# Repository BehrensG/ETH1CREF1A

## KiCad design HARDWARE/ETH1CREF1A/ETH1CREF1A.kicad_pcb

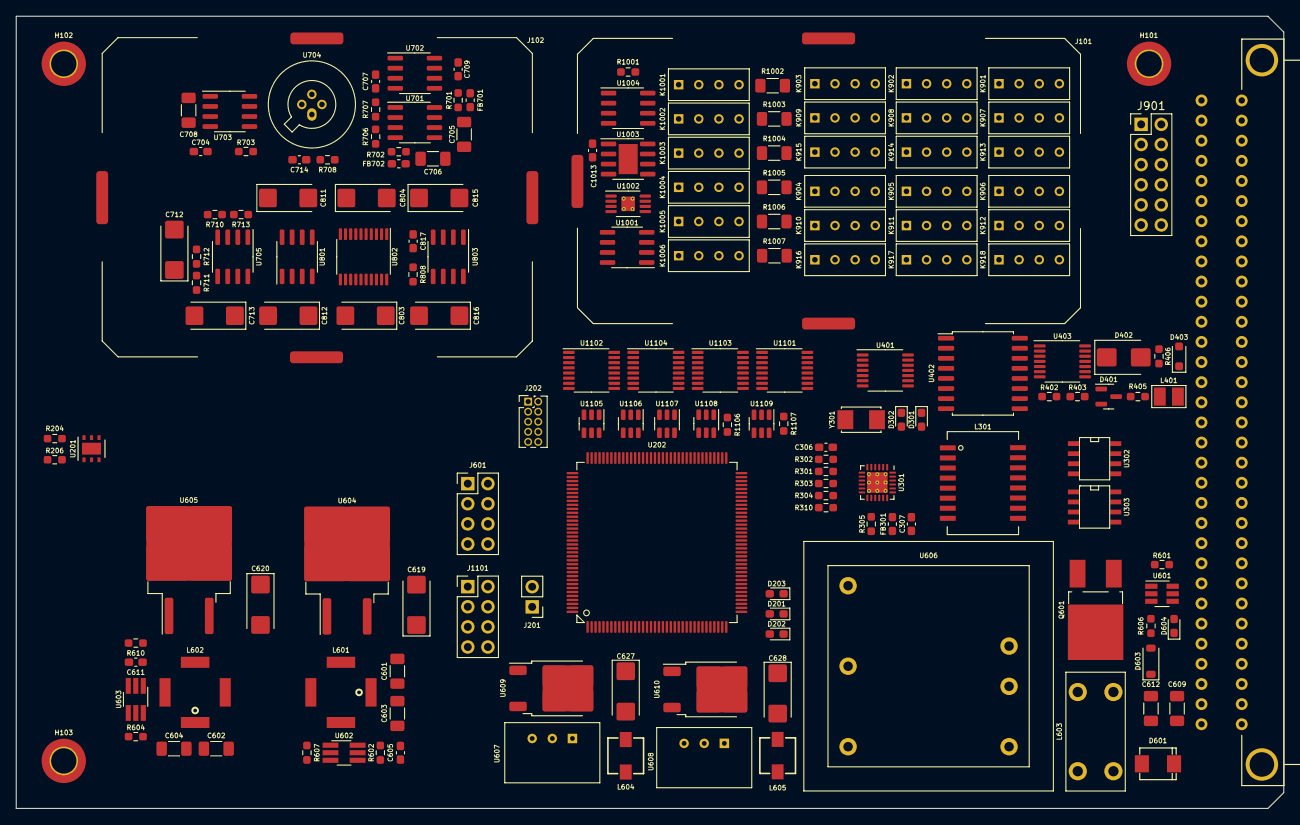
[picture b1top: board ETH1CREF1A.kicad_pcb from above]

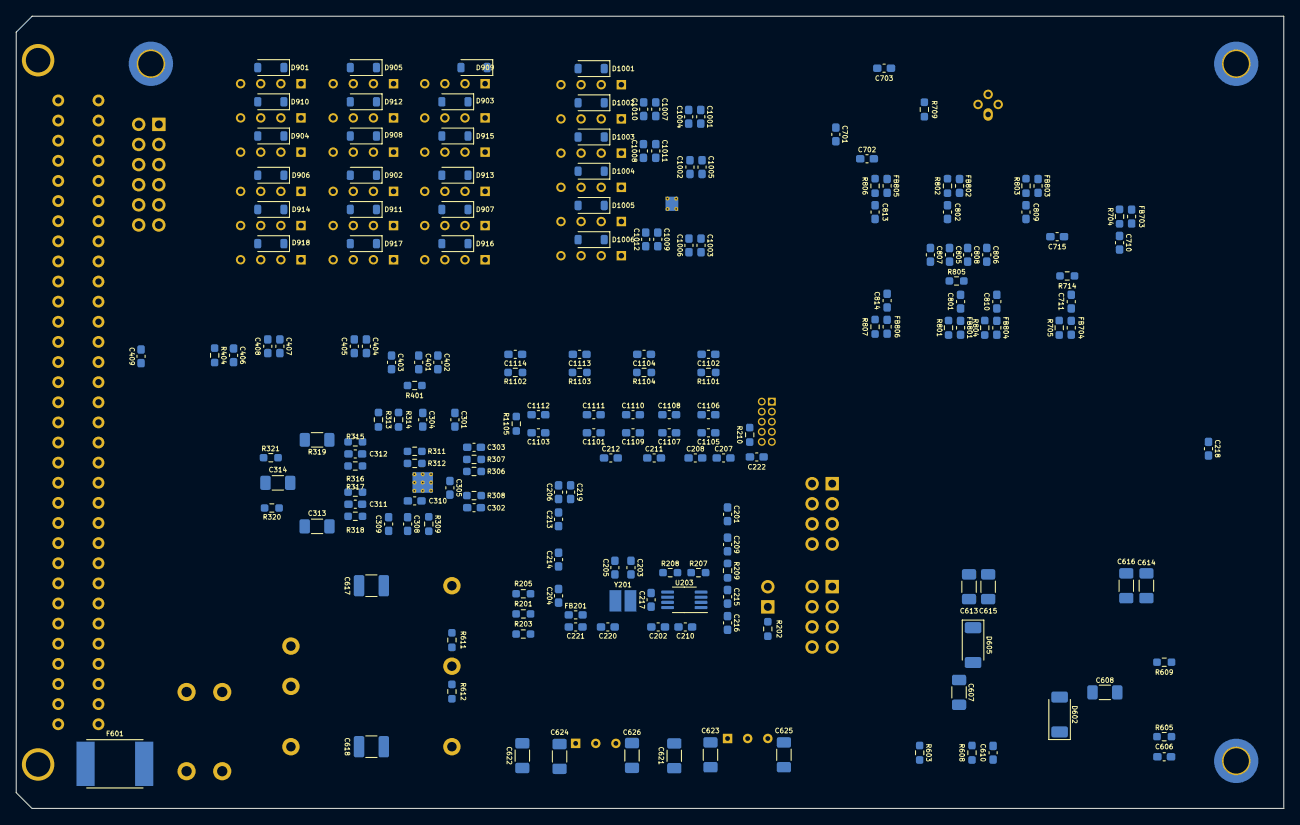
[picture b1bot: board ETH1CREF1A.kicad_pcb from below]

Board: 4 copper layers, 160.0 x 100.0 mm, 352 parts (186 on the bottom side), 209 nets, no tracks yet.

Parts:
C201, C202, C204, C207, C209, C211, C212, C213, C214, C215, C216, C217, C218, C219, C220, C222, C302, C305, C308, C309, C310, C311, C312, C401, C403, C404, C406, C408, C701, C702, C704, C710, C711, C714, C801, C802, C805, C806, C809, C810, C813, C814, C1001, C1002, C1003, C1007, C1008, C1009, C1101, C1102, C1103, C1104, C1105, C1106, C1107, C1108, C1109, C1110, C1111, C1112, C1113, C1114: 100n; C_0603_1608Metric_Pad1.08x0.95mm_HandSolder
C203, C205, C301, C304: 8p; C_0603_1608Metric_Pad1.08x0.95mm_HandSolder
C206, C208, C703, C707, C709: 2u2; C_0603_1608Metric_Pad1.08x0.95mm_HandSolder
C210, C221, C306, C307, C402, C405, C407, C605, C606, C807, C808, C1004, C1005, C1006, C1010, C1011, C1012: 1u; C_0603_1608Metric_Pad1.08x0.95mm_HandSolder
C303: 470p; C_0603_1608Metric_Pad1.08x0.95mm_HandSolder
C313, C314: 1n/1kV; C_1206_3216Metric_Pad1.33x1.80mm_HandSolder
C409: 47p; C_0603_1608Metric_Pad1.08x0.95mm_HandSolder
C601, C602, C621, C622, C623, C624: 10u/50V; C_1206_3216Metric_Pad1.33x1.80mm_HandSolder
C603, C604, C613, C614, C615, C616: 4u7/50V; C_1206_3216Metric_Pad1.33x1.80mm_HandSolder
C607, C608: 1u/HC; C_1206_3216Metric_Pad1.33x1.80mm_HandSolder
C609, C612: 2u2/50V; C_1206_3216Metric_Pad1.33x1.80mm_HandSolder
C610, C611: 4p7; C_0603_1608Metric_Pad1.08x0.95mm_HandSolder
C617, C618: 330p/2kV; C_1210_3225Metric_Pad1.33x2.70mm_HandSolder
C619, C620, C627, C628, C712, C713, C803, C804, C811, C812, C815, C816: 10u/35V; CP_EIA-6032-28_Kemet-C_Pad2.25x2.35mm_HandSolder
C625, C626: 10u/16V; C_1206_3216Metric_Pad1.33x1.80mm_HandSolder
C705, C706, C708: 10u/35V; C_1206_3216Metric_Pad1.33x1.80mm_HandSolder
C715, C817: 10p; C_0603_1608Metric_Pad1.08x0.95mm_HandSolder
C1013: 200p; C_0603_1608Metric_Pad1.08x0.95mm_HandSolder
D201: BLUE; LED_0603_1608Metric_Pad1.05x0.95mm_HandSolder
D202, D604: RED; LED_0603_1608Metric_Pad1.05x0.95mm_HandSolder
D203, D302: GREEN; LED_0603_1608Metric_Pad1.05x0.95mm_HandSolder
D301: YELLOW; LED_0603_1608Metric_Pad1.05x0.95mm_HandSolder
D401: BAV99; SOT-23
D402: SMBJ5.0A; D_SMB
D403: SD36C-01FTG; D_SOD-323_HandSoldering
D601: SM6T30AY; DO_214AA_REV
D602, D605: PMEG6010EP,115; D_SOD-128
D603: MMSZ5249B; D_SOD-123
D901, D902, D903, D904, D905, D906, D907, D908, D909, D910, D911, D912, D913, D914, D915, D916, D917, D918, D1001, D1002, D1003, D1004, D1005, D1006: 1N4148W; D_SOD-123
F601: MF-LSMF185/33X; Fuse_SMD2920
FB201, FB301, FB701, FB702, FB703, FB704, FB801, FB802, FB803, FB804, FB805, FB806: 600; L_0603_1608Metric_Pad1.05x0.95mm_HandSolder
H101, H102, H103: MountingHole; MountingHole_3.2mm_M3_DIN965_Pad_TopBottom
J101: MS638-10F
J102: MS548-10F
J201: Conn_02x01; PinHeader_1x02_P2.54mm_Vertical
J202: 20021111-00010T4LF; PinHeader_2x05_P1.27mm_Vertical
J501: C64AC; Socket_DIN41612-CaseC1-AC-Male-64Pin-2rows
J601, J1101: Conn_02x04_Odd_Even; PinHeader_2x04_P2.54mm_Vertical
J901: Conn_02x06_Odd_Even; PinHeader_2x06_P2.54mm_Vertical
K901, K902, K903, K904, K905, K906, K907, K908, K909, K910, K911, K912, K913, K914, K915, K916, K917, K918, K1001, K1002, K1003, K1004, K1005, K1006: 9012
L301: 749010012A
L401: CW252016-R33G; CW252016
L601, L602: 74489440068
L603: 7448014501
L604, L605: TCK-141
Q601: IRFR5410; TO-252-2_Rectifier
R201, R205: 680; R_0603_1608Metric_Pad0.98x0.95mm_HandSolder
R202, R209, R210, R303, R306, R307, R308, R309, R311, R401, R805, R1101, R1102, R1103, R1104: 10k; R_0603_1608Metric_Pad0.98x0.95mm_HandSolder
R203: 560; R_0603_1608Metric_Pad0.98x0.95mm_HandSolder
R204, R206, R207, R208: 4k7; R_0603_1608Metric_Pad0.98x0.95mm_HandSolder
R301, R302, R304, R305: 33; R_0603_1608Metric_Pad0.98x0.95mm_HandSolder
R310: 1k5; R_0603_1608Metric_Pad0.98x0.95mm_HandSolder
R312: 12k1; R_0603_1608Metric_Pad0.98x0.95mm_HandSolder
R313, R314: 270; R_0603_1608Metric_Pad0.98x0.95mm_HandSolder
R315, R316, R317, R318: 49R9; R_0603_1608Metric_Pad0.98x0.95mm_HandSolder
R319: 1M/1kV; R_1206_3216Metric_Pad1.30x1.75mm_HandSolder
R320, R321: 75/1%; R_0603_1608Metric_Pad0.98x0.95mm_HandSolder
R402: 14k7; R_0603_1608Metric_Pad0.98x0.95mm_HandSolder
R403: 100; R_0603_1608Metric_Pad0.98x0.95mm_HandSolder
R404, R1106: 1k; R_0603_1608Metric_Pad0.98x0.95mm_HandSolder
R405: 47; R_0603_1608Metric_Pad0.98x0.95mm_HandSolder
R406: 51R1; R_0603_1608Metric_Pad0.98x0.95mm_HandSolder
R601: 100k; R_0603_1608Metric_Pad0.98x0.95mm_HandSolder
R602, R604, R607, R609: 1M; R_0603_1608Metric_Pad0.98x0.95mm_HandSolder
R603, R605: 287k; R_0603_1608Metric_Pad0.98x0.95mm_HandSolder
R606: 330; R_0603_1608Metric_Pad0.98x0.95mm_HandSolder
R608: 97k6; R_0603_1608Metric_Pad0.98x0.95mm_HandSolder
R610: 46k4; R_0603_1608Metric_Pad0.98x0.95mm_HandSolder
R611, R612: OPT; R_0603_1608Metric_Pad0.98x0.95mm_HandSolder
R701, R702, R704, R705, R801, R802, R803, R804, R806, R807: 10; R_0603_1608Metric_Pad0.98x0.95mm_HandSolder
R703, R709, R808, R1105, R1107: 0; R_0603_1608Metric_Pad0.98x0.95mm_HandSolder
R706: 5k/.1%; R_0603_1608Metric_Pad0.98x0.95mm_HandSolder
R707: 2k/.1%; R_0603_1608Metric_Pad0.98x0.95mm_HandSolder
R708: 7k5; R_0603_1608Metric_Pad0.98x0.95mm_HandSolder
R710: 6k98/.1%; R_0603_1608Metric_Pad0.98x0.95mm_HandSolder
R711, R714: 10k/.1%; R_0603_1608Metric_Pad0.98x0.95mm_HandSolder
R712: 1k96/.1%; R_0603_1608Metric_Pad0.98x0.95mm_HandSolder
R713: 3k01/.1%; R_0603_1608Metric_Pad0.98x0.95mm_HandSolder
R1001: 2k; R_0603_1608Metric_Pad0.98x0.95mm_HandSolder
R1002: TNPV12061M00BYEN; R_1206_3216Metric_Pad1.30x1.75mm_HandSolder
R1003: TNPU1206100KBZEN00; R_1206_3216Metric_Pad1.30x1.75mm_HandSolder
R1004: TNPU120610K0AWEN00; R_1206_3216Metric_Pad1.30x1.75mm_HandSolder
R1005: TNPU12061K00AWEN00; R_1206_3216Metric_Pad1.30x1.75mm_HandSolder
R1006: TNPU1206100RAZEN00; R_1206_3216Metric_Pad1.30x1.75mm_HandSolder
R1007: RNCF1206AKT10R0; R_1206_3216Metric_Pad1.30x1.75mm_HandSolder
U201: HDC1080; Texas_PWSON-N6
U202: STM32F429ZIT; TQFP-144_20x20mm_P0.5mm
U203: 24LC08B-E/MS; MSOP-8_3x3mm_P0.65mm
U301: LAN8742A; QFN-24-1EP_4x4mm_P0.5mm_EP2.6x2.6mm_ThermalVias
U302, U303: LC03-3.3; SO8E
U401: TXB0104PW; TSSOP-14_4.4x5mm_P0.65mm
U402: ADuM5402; SOIC-16W_7.5x10.3mm_P1.27mm
U403: 74AC125; TSSOP-14_4.4x5mm_P0.65mm
U601: MAX5902; SOT-23-6_Handsoldering
U602, U603: LT8330_S6; TSOT-23-6_HandSoldering
U604: MC7815CD2TG; TO-263-2
U605: MC7915CD2TR4G; TO-263-2
U606: THL15-2415WI; THL15
U607: TSR1-2490; TSR1
U608: TSR1-2450; TSR1
U609: LM1117DTX-5/NOPB; TO-252-2
U610: LM1117DTX-3.3/NOPB; TO-252-2
U701, U705, U801: AD8676BRZ; SOIC-8_3.9x4.9mm_P1.27mm
U702: MAX6350ESA+; SOIC-8_3.9x4.9mm_P1.27mm
U703: LT1021DCS8-7#PBF; SOIC-8_3.9x4.9mm_P1.27mm
U704: LM399H; LMx99
U802: AD5791ARUZ; TSSOP-20_4.4x6.5mm_P0.65mm
U803: AD8675ARZ; SOIC-8_3.9x4.9mm_P1.27mm
U1001: DG419DY; SOIC-8_3.9x4.9mm_P1.27mm
U1002: LT5400-3; MSOP-8-1EP_3x3mm_P0.65mm_EP1.73x1.85mm_ThermalVias
U1003: ADA4898-2; SOIC-8-1EP_3.9x4.9mm_P1.27mm_EP2.41x3.81mm
U1004: AD811JRZ; SOIC-8_3.9x4.9mm_P1.27mm
U1101, U1102, U1103, U1104: 74HCT595PW; TSSOP-16_4.4x5mm_P0.65mm
U1105, U1106, U1107, U1108, U1109: SN74LVC1T45DRLR; SOT-23-6
Y201: NX5032GA-16.000M; NX3225GD
Y301: NX5032GA-25.000000MHZ-LN-CD-1; NX5032GA

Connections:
+3.3V: C201.1, C202.1, C204.1, C207.1, C209.1, C210.1, C211.1, C212.1, C213.1, C214.1, C215.1, C216.1, C217.1, C218.1, C219.1, C220.1, C302.1, C305.1, C401.1, C402.1, C628.1, C806.1, C808.1, C1101.1, C1103.1, C1105.1, C1107.1, C1109.1, D201.2 (A), D202.2 (A), D203.2 (A), FB201.1, FB301.1, J202.1, J601.4, R202.2, R204.1, R206.1, R207.1, R208.1, R210.1, R306.1, R307.1, R308.1, R309.1, R310.1, R401.1, R805.2, U201.5 (VCC), U202.6 (VBAT), U202.17 (VDD), U202.30 (VDD), U202.39 (VDD), U202.52 (VDD), U202.62 (VDD), U202.72 (VDD), U202.84 (VDD), U202.95 (VDDUSB), U202.108 (VDD), U202.121 (VDD), U202.131 (VDD), U202.143 (PDR_ON), U202.144 (VDD), U203.8 (VCC), U301.9 (VDDIO), U401.1 (VCCA), U610.2 (VO), U802.6 (~RESET), U802.7 (~CLR), U802.10 (IOVCC), U1105.6 (VCCB), U1106.6 (VCCB), U1107.6 (VCCB), U1108.6 (VCCB), U1109.6 (VCCB)
+5V: C403.1, C404.1, C405.1, C627.1, C805.1, C807.1, C1102.1, C1104.1, C1106.1, C1108.1, C1110.1, C1111.1, C1112.1, C1113.1, C1114.1, D901.1 (K), D902.1 (K), D903.1 (K), D904.1 (K), D905.1 (K), D906.1 (K), D907.1 (K), D908.1 (K), D909.1 (K), D910.1 (K), D911.1 (K), D912.1 (K), D913.1 (K), D914.1 (K), D915.1 (K), D916.1 (K), D917.1 (K), D918.1 (K), D1001.1 (K), D1002.1 (K), D1003.1 (K), D1004.1 (K), D1005.1 (K), D1006.1 (K), J601.2, K901.2, K902.2, K903.2, K904.2, K905.2, K906.2, K907.2, K908.2, K909.2, K910.2, K911.2, K912.2, K913.2, K914.2, K915.2, K916.2, K917.2, K918.2, K1001.2, K1002.2, K1003.2, K1004.2, K1005.2, K1006.2, R1101.2, R1102.2, R1103.2, R1104.2, R1106.2, U401.14 (VCCB), U402.1 (VDD1), U609.2 (VO), U802.9 (VCC), U1001.5 (VL), U1101.10 (~SRCLR), U1101.16 (VCC), U1102.10 (~SRCLR), U1102.16 (VCC), U1103.10 (~SRCLR), U1103.16 (VCC), U1104.10 (~SRCLR), U1104.16 (VCC), U1105.1 (VCCA), U1106.1 (VCCA), U1107.1 (VCCA), U1108.1 (VCCA), U1109.1 (VCCA)
+5V_TRIG: C406.1, C407.1, C408.1, R404.1, U402.10 (VSEL), U402.16 (VISO), U403.14 (VCC)
+15VF: C619.1, C703.1, C704.1, C708.1, C1007.1, C1008.1, C1009.1, C1010.1, C1011.1, C1012.1, FB701.1, FB704.1, FB802.1, FB803.1, FB806.1, J601.1, R701.1, R705.1, R708.1, R802.1, R803.1, R807.1, U604.3 (OUT), U702.2 (IN), U703.2 (Vin), U704.3, U1001.4 (V+), U1003.8 (V+), U1004.7 (V+)
+24V: F601.1, J501.A31 (31A), J501.A32 (32A), J501.C31 (31C), J501.C32 (32C)
+24VF: C601.1, C602.1, C603.1, C604.1, C617.1, C621.1, C622.1, L601.1, L602.1, L604.1, L605.1, R602.1, R604.1, R611.1, U602.6 (VIN), U603.6 (VIN), U606.3 (+VOUT)
-15VF: C620.2, C1001.1, C1002.1, C1003.1, C1004.1, C1005.1, C1006.1, FB702.1, FB703.1, FB801.1, FB804.1, FB805.1, J601.3, R702.1, R704.1, R801.1, R804.1, R806.1, U605.3 (VO), U704.4, U1001.7 (V-), U1003.4 (V-), U1003.9 (EP), U1004.4 (V-)
/Connect/EXT_TRIG: C409.1, D403.1 (A1), J501.A16 (16A), L401.1
/Connect/RX+: J501.A20 (20A), U303.8
/Connect/RX-: J501.A21 (21A), U303.5
/Connect/TX+: J501.C20 (20C), U302.8
/Connect/TX-: J501.C21 (21C), U302.5
/Current Source/AOUT: K907.1, K908.1, K909.1, K910.1, K911.1, K912.1, R1002.2, R1003.2, R1004.2, R1005.2, R1006.2, R1007.2, U1003.5 (+)
/Current Source/CS_SEL_R1Meg: D1001.2 (A), K1001.3, U1104.15 (QA)
/Current Source/CS_SEL_R1k: D1004.2 (A), K1004.3, U1104.3 (QD)
/Current Source/CS_SEL_R10: D1006.2 (A), K1006.3, U1104.5 (QF)
/Current Source/CS_SEL_R10k: D1003.2 (A), K1003.3, U1104.2 (QC)
/Current Source/CS_SEL_R100: D1005.2 (A), K1005.3, U1104.4 (QE)
/Current Source/CS_SEL_R100k: D1002.2 (A), K1002.3, U1104.1 (QB)
/Current Source/CS_SEL_VSOUR: U1001.6, U1104.6 (QG)
/Current Source/VOUT: C817.2, K901.1, K902.1, K903.1, K904.1, K905.1, K906.1, R808.2, U803.6, U1001.8
/DAC/DAC_+15V: C802.1, C804.1, FB802.2, R802.2, U802.5 (VDD)
/DAC/DAC_-15V: C801.1, C803.2, FB801.2, R801.2, U802.18 (VSS)
/DAC/OPAMP_+15V: C814.1, C816.1, FB806.2, R807.2, U803.7 (V+)
/DAC/OPAMP_-15V: C813.1, C815.1, FB805.2, R806.2, U803.4 (V-)
/DAC/REF_-10V: R714.2, U705.7, U801.3 (+)
/DAC/SCLK: U202.111 (PC10,SPI3_SCK,I2S3_CK,USART3_TX,UART4_T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), U802.13 (SCLK)
/DAC/SDIN: U202.113 (PC12,SPI3_MOSI,I2S3_SD,USART3_CK,UART5_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), U802.12 (SDIN)
/DAC/SDO: U202.112 (PC11,I2S3ext_SD,SPI3_MISO,USART3_RX,UAR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), U802.11 (SDO)
/DAC/~SYNC: R805.1, U202.110 (PA15,JTDI,TIM2_CH1,TIM2_ETR,SPI1_NSS,SP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), U802.14 (~SYNC)
/Ethernet/ETH_RXN: L301.8 (RD-), R318.2, U301.22 (RXN)
/Ethernet/ETH_RXP: L301.6 (RD+), R317.2, U301.23 (RXP)
/Ethernet/ETH_TXN: L301.3 (TD-), R316.2, U301.20 (TXN)
/Ethernet/ETH_TXP: L301.1 (TD+), R315.2, U301.21 (TXP)
/Ethernet/MODE0: R301.1, R306.2, U301.8 (RXD0/MODE0)
/Ethernet/MODE1: R302.1, R307.2, U301.7 (RXD1/MODE1)
/Ethernet/MODE2: R304.1, R308.2, U301.11 (CRS_DV/MODE2)
/Ethernet/REFCLK0: R305.1, R309.2, U301.14 (~INT/REFCLK0)
/Ethernet/REF_CLK: R305.2, U202.35 (PA1,TIM2_CH2,TIM5_CH2,USART2_RTS,UART4_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)
/Ethernet/RMII_CRS_DV: R304.2, U202.43 (PA7,TIM1_CH1N,TIM3_CH2,TIM8_CH1N,SPI1_M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)
/Ethernet/RMII_MDC: U202.27 (PC1,ETH_MDC,EVENTOUT,ADC1_IN11,ADC2_IN1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), U301.13 (MDC)
/Ethernet/RMII_MDIO: R310.2, U202.36 (PA2,TIM2_CH3,TIM5_CH3,TIM9_CH1,USART2_T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), U301.12 (MDIO)
/Ethernet/RMII_RXD0: R301.2, U202.44 (PC4,ETH_MII_RXD0,ETH__RMII_RXD0,EVENTOU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)
/Ethernet/RMII_RXD1: R302.2, U202.45 (PC5,ETH_MII_RXD1,ETH__RMII_RXD1,EVENTOU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)
/Ethernet/RMII_TXD0: U202.128 (PG13,SPI6_SCK,USART6_CTS,ETH_MII_TXD0,E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), U301.17 (TXD0)
/Ethernet/RMII_TXD1: U202.129 (PG14,SPI6_MOSI,USART6_TX,ETH_MII_TXD1,E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), U301.18 (TXD1)
/Ethernet/RMII_TXEN: U202.126 (PG11,ETH_MII_TX_EN,ETH__RMII_TX_EN,FMC_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), U301.16 (TXEN)
/GPIO/MODE_I2C_SCL: J1101.1, U202.100 (PA8,MCO1,TIM1_CH1,I2C3_SCL,USART1_CK,OT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)
/GPIO/MODE_I2C_SDA: J1101.3, U202.99 (PC9,MCO2,TIM3_CH4,TIM8_CH4,I2C3_SDA,I2S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)
/GPIO/QH: U202.75 (PB14,TIM1_CH2N,TIM8_CH2N,SPI2_MISO,I2S2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), U1108.4 (B)
/GPIO/RCLK: U202.73 (PB12,TIM1_BKIN,I2C2_SMBA,SPI2_NSS,I2S2_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), U1107.4 (B)
/GPIO/SER: U202.76 (PB15,RTC_REFIN,TIM1_CH3N,TIM8_CH3N,SPI2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), U1105.4 (B)
/GPIO/SPI5_MISO: J1101.4, U202.20 (PF8,SPI5_MISO,SAI1_SCK_B,TIM13_CH1,FMC_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)
/GPIO/SPI5_MOSI: J1101.6, U202.21 (PF9,SPI5_MOSI,SAI1_FS_B,TIM14_CH1,FMC_C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)
/GPIO/SPI5_SCK: J1101.2, U202.19 (PF7,TIM11_CH1,SPI5_SCK,SAI1_MCLK_B,UART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)
/GPIO/SRCLK: U202.74 (PB13,TIM1_CH1N,SPI2_SCK,I2S2_CK,USART3_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), U1106.4 (B)
/GPIO/nOE: U202.70 (PB11,TIM2_CH4,I2C2_SDA,USART3_RX,OTG_HS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), U1109.4 (B)
/GPIO/relay0: D901.2 (A), K901.3, U1104.7 (QH)
/GPIO/relay1: D906.2 (A), K906.3, U1103.15 (QA)
/GPIO/relay2: D911.2 (A), K911.3, U1103.1 (QB)
/GPIO/relay3: D916.2 (A), K916.3, U1103.2 (QC)
/GPIO/relay4: D902.2 (A), K902.3, U1103.3 (QD)
/GPIO/relay5: D907.2 (A), K907.3, U1103.4 (QE)
/GPIO/relay6: D912.2 (A), K912.3, U1103.5 (QF)
/GPIO/relay7: D915.2 (A), K915.3, U1103.6 (QG)
/GPIO/relay8: D903.2 (A), K903.3, U1103.7 (QH)
/GPIO/relay9: D908.2 (A), K908.3, U1101.15 (QA)
/GPIO/relay10: D913.2 (A), K913.3, U1101.1 (QB)
/GPIO/relay11: D917.2 (A), K917.3, U1101.2 (QC)
/GPIO/relay12: D904.2 (A), K904.3, U1101.3 (QD)
/GPIO/relay13: D909.2 (A), K909.3, U1101.4 (QE)
/GPIO/relay14: D914.2 (A), K914.3, U1101.5 (QF)
/GPIO/relay15: D918.2 (A), K918.3, U1101.6 (QG)
/GPIO/relay16: D905.2 (A), K905.3, U1101.7 (QH)
/GPIO/relay17: D910.2 (A), K910.3, U1102.15 (QA)
/MCU/EEPROM_SCL: R208.2, U202.11 (PF1,I2C2_SCL,FMC_A1,EVENTOUT), U203.6 (SCL)
/MCU/EEPROM_SDA: R207.2, U202.10 (PF0,I2C2_SDA,FMC_A0,EVENTOUT), U203.5 (SDA)
/MCU/EEPROM_WP: U202.89 (PG4,FMC_A14,FMC_BA0,EVENTOUT), U203.7 (WP)
/MCU/LED_BLUE: R201.1, U202.48 (PB2,BOOT1,EVENTOUT)
/MCU/LED_GREEN: R205.1, U202.50 (PF12,FMC_A6,EVENTOUT)
/MCU/LED_RED: R203.1, U202.49 (PF11,SPI5_MOSI,FMC_SDNRAS,DCMI_D12,EVEN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)
/MCU/MCU_DEFAULT: J201.1, R202.1, U202.63 (PE10,TIM1_CH2N,FMC_D7,EVENTOUT)
/MCU/MCU_VDDA: C221.1, FB201.2, U202.32 (VREF+), U202.33 (VDDA)
/MCU/NRST: C222.1, J202.10, R210.2, U202.25 (NRST), U301.15 (~RST)
/MCU/SENS_SCL: R204.2, U201.6 (SCL), U202.136 (PB6,TIM4_CH1,I2C1_SCL,USART1_TX,CAN2_TX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)
/MCU/SENS_SDA: R206.2, U201.1 (SDA), U202.137 (PB7,TIM4_CH2,I2C1_SDA,USART1_RX,FMC_NL,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)
/MCU/TCK_SWCLK: J202.4, U202.109 (PA14,JTCK-SWCLK,EVENTOUT)
/MCU/TMS_SWDIO: J202.2, U202.105 (PA13,JTMS-SWDIO,EVENTOUT)
/MCU/TRIG_EN: U202.60 (PE9,TIM1_CH1,FMC_D6,EVENTOUT), U401.2 (A1)
/MCU/TRIG_IN: U202.58 (PE7,TIM1_ETR,UART7_Rx,FMC_D4,EVENTOUT), U401.4 (A3)
/MCU/TRIG_OUT: U202.59 (PE8,TIM1_CH1N,UART7_Tx,FMC_D5,EVENTOUT), U401.3 (A2)
/Reference Voltage/REF_+10V: C715.2, R711.1, R712.2, R713.2, U705.1, U801.5 (+)
/Relays/A_AOUT: J501.A2 (2A), J501.C2 (2C), J901.1, J901.2, K901.4, K907.4, K913.4
/Relays/B_AOUT: J501.A3 (3A), J501.C3 (3C), J901.3, J901.4, K902.4, K908.4, K914.4
/Relays/C_AOUT: J501.A4 (4A), J501.C4 (4C), J901.5, J901.6, K903.4, K909.4, K915.4
/Relays/D_AOUT: J501.A5 (5A), J501.C5 (5C), J901.7, J901.8, K904.4, K910.4, K916.4
/Relays/E_AOUT: J501.A6 (6A), J501.C6 (6C), J901.9, J901.10, K905.4, K911.4, K917.4
/Relays/F_AOUT: J501.A7 (7A), J501.C7 (7C), J901.11, J901.12, K906.4, K912.4, K918.4
/Trigger/EXT_TRIG_SIGN: R402.1, U402.12 (VIC), U403.3 (O)
/Trigger/TRIG_OUT_EN: U402.14 (VOA), U403.4 (EN), U403.10 (EN), U403.13 (EN)
/Trigger/TRIG_OUT_SIGN: U402.13 (VOB), U403.5 (D), U403.9 (D), U403.12 (D)
AGNDF: C201.2, C202.2, C203.2, C204.2, C205.2, C206.2, C207.2, C208.2, C209.2, C210.2, C211.2, C212.2, C213.2, C214.2, C215.2, C216.2, C217.2, C218.2, C219.2, C220.2, C221.2, C222.2, C301.2, C302.2, C303.2, C304.2, C305.2, C306.2, C307.2, C308.2, C309.2, C310.2, C311.2, C312.2, C313.2, C401.2, C402.2, C403.2, C404.2, C405.2, C601.2, C602.2, C603.2, C604.2, C605.2, C606.2, C613.2, C614.2, C615.2, C616.2, C618.1, C619.2, C620.1, C621.2, C622.2, C623.2, C624.2, C625.2, C626.2, C627.2, C628.2, C701.2, C702.2, C703.2, C704.2, C705.2, C706.2, C707.2, C708.2, C709.2, C710.2, C711.2, C712.1, C713.2, C714.2, C801.2, C802.2, C803.1, C804.2, C805.2, C806.2, C807.2, C808.2, C809.2, C810.2, C811.2, C812.2, C813.2, C814.2, C815.2, C816.2, C1001.2, C1002.2, C1003.2, C1004.2, C1005.2, C1006.2, C1007.2, C1008.2, C1009.2, C1010.2, C1011.2, C1012.2, C1101.2, C1102.2, C1103.2, C1104.2, C1105.2, C1106.2, C1107.2, C1108.2, C1109.2, C1110.2, C1111.2, C1112.2, C1113.2, C1114.2, D602.1 (K), J101.1 (Shield), J102.1 (Shield), J201.2, J202.3, J202.5, J601.5, J601.6, J601.7, J601.8, J1101.5, J1101.7, J1101.8, K913.1, K914.1, K915.1, K916.1, K917.1, K918.1, L601.3, R209.2, R303.2, R311.2, R312.1, R313.2, R314.2, R319.2, R603.2, R605.2, R608.2, R610.2, R612.2, R706.1, R710.1, R1105.2, U201.2 (GND), U202.16 (VSS), U202.31 (VSSA), U202.38 (VSS), U202.51 (VSS), U202.61 (VSS), U202.83 (VSS), U202.94 (VSS), U202.107 (VSS), U202.120 (VSS), U202.130 (VSS), U203.1 (A0), U203.2 (A1), U203.3 (A2), U203.4 (GND), U301.25 (VSS), U401.7 (GND), U402.2 (GND1), U402.8 (GND1), U602.2 (GND), U603.2 (GND), U604.2 (GND), U605.1 (GND), U606.5 (-VOUT), U607.2 (GND), U608.2 (GND), U609.1 (GND), U610.1 (GND), U701.5 (+), U702.4 (GND), U703.4 (GND), U704.2, U705.5 (+), U802.8 (~LDAC), U802.15 (DGND), U802.19 (AGND), U1001.2, U1001.3 (GND), U1002.8, U1002.9, U1101.8 (GND), U1102.8 (GND), U1103.8 (GND), U1104.8 (GND), U1105.2 (GND), U1105.5 (DIR), U1106.2 (GND), U1106.5 (DIR), U1107.2 (GND), U1107.5 (DIR), U1108.2 (GND), U1109.2 (GND), U1109.5 (DIR)
Earth: C313.1, C314.2, J501.A18 (18A), J501.A22 (22A), J501.C18 (18C), J501.C22 (22C), R319.1
GNDPWR: C609.2, C612.2, D601.2 (A), D604.1 (K), J501.A27 (27A), J501.A28 (28A), J501.C27 (27C), J501.C28 (28C), L603.1, U601.4 (GND)
GND_TRIG: C406.2, C407.2, C408.2, D401.1 (K), D402.2 (A), D403.2 (A2), J501.C16 (16C), R406.2, U402.9 (GNDISO), U402.15 (GNDISO), U403.1 (EN), U403.7 (GND)
unnamed: C314.1, R320.2, R321.2
unnamed: C409.2, R406.1
unnamed: D201.1 (K), R201.2
unnamed: D202.1 (K), R203.2
unnamed: D203.1 (K), R205.2
unnamed: D301.2 (A), R311.1, U301.2 (LED2/~INTSEL)
unnamed: D301.1 (K), R313.1
unnamed: D302.2 (A), U301.3 (LED1/REGOFF)
unnamed: D302.1 (K), R314.1
unnamed: D401.2 (A), D402.1 (K), R404.2
unnamed: D601.1 (K), F601.2, Q601.3 (S), R601.1, U601.1 (VS)
unnamed: C608.1, D602.2 (A), L602.2
unnamed: D603.2 (A), R606.1
unnamed: C609.1, C612.1, D603.1 (K), L603.2, Q601.2 (D), U601.2 (DRAIN)
unnamed: D604.2 (A), R606.2
unnamed: C607.1, D605.2 (A), L601.2
unnamed: C610.1, C613.1, C615.1, D605.1 (K), R607.1, U604.1 (IN)
unnamed: K1001.1, K1002.1, K1003.1, K1004.1, K1005.1, K1006.1, R1001.2, U1002.7, U1004.6
unnamed: K1001.4, R1002.1
unnamed: K1002.4, R1003.1
unnamed: K1003.4, R1004.1
unnamed: K1004.4, R1005.1
unnamed: K1005.4, R1006.1
unnamed: K1006.4, R1007.1
unnamed: L301.10 (CRX), R320.1
unnamed: L301.15 (CTX), R321.1
unnamed: L301.11 (RX+), U303.1
unnamed: L301.9 (RX-), U303.4
unnamed: L301.16 (TX+), U302.1
unnamed: L301.14 (TX-), U302.4
unnamed: L401.2, R405.2
unnamed: Q601.1 (G), U601.3 (GATE)
unnamed: R707.2, R709.2, U701.1
unnamed: R209.1, U202.138 (BOOT0)
unnamed: C203.1, U202.23 (PH0,EVENTOUT,OSC_IN), Y201.1
unnamed: C205.1, U202.24 (PH1,EVENTOUT,OSC_OUT), Y201.2
unnamed: C206.1, U202.71 (VCAP_1)
unnamed: C208.1, U202.106 (VCAP_2)
unnamed: R312.2, U301.24 (RBIAS)
unnamed: R303.1, U301.10 (RXER/PHYAD0)
unnamed: C303.1, C306.1, U301.6 (VDDCR)
unnamed: C301.1, U301.5 (XTAL1/CLKIN), Y301.2
unnamed: C304.1, U301.4 (XTAL2), Y301.1
unnamed: U401.13 (B1), U402.3 (VIA)
unnamed: U401.12 (B2), U402.4 (VIB)
unnamed: U401.11 (B3), U402.5 (VOC)
unnamed: R401.2, U401.8 (OE)
unnamed: R402.2, R403.1, U403.2 (D)
unnamed: D401.3 (K), R403.2, R405.1, U403.6 (O), U403.8 (O), U403.11 (O)
unnamed: R601.2, U601.6 (ON/~OFF)
unnamed: R602.2, R603.1, U602.4 (EN/UVLO)
unnamed: C610.2, R607.2, R608.1, U602.3 (FBX)
unnamed: C605.1, U602.5 (INTVCC)
unnamed: C607.2, L601.4, U602.1 (SW)
unnamed: R604.2, R605.1, U603.4 (EN/UVLO)
unnamed: C611.2, R609.2, R610.1, U603.3 (FBX)
unnamed: C606.1, U603.5 (INTVCC)
unnamed: C608.2, L602.4, U603.1 (SW)
unnamed: C611.1, C614.1, C616.1, L602.3, R609.1, U605.2 (VI)
unnamed: C617.2, L603.3, U606.1 (+VIN)
unnamed: C618.2, L603.4, U606.2 (-VIN)
unnamed: R611.2, R612.1, U606.4 (TRIM)
unnamed: C623.1, L604.2, U607.1 (VI)
unnamed: C625.1, U607.3 (VO), U609.3 (VI)
unnamed: C624.1, L605.2, U608.1 (VI)
unnamed: C626.1, U608.3 (VO), U610.3 (VI)
unnamed: C709.1, U701.3 (+), U702.6 (OUT)
unnamed: R706.2, R707.1, U701.2 (-)
unnamed: U701.6 (-), U701.7
unnamed: C701.1, C705.1, FB701.2, R701.2, U701.8 (V+)
unnamed: C702.1, C706.1, FB702.2, R702.2, U701.4 (V-)
unnamed: C707.1, U702.3 (NR)
unnamed: R703.2, U703.6 (Vout)
unnamed: C714.1, R703.1, R708.2, R709.1, R712.1, U704.1, U705.3 (+)
unnamed: C715.1, R710.2, R713.1, U705.2 (-)
unnamed: R711.2, R714.1, U705.6 (-)
unnamed: C711.1, C713.1, FB704.2, R705.2, U705.8 (V+)
unnamed: C710.1, C712.2, FB703.2, R704.2, U705.4 (V-)
unnamed: U801.2 (-), U802.17 (VREFNS)
unnamed: U801.6 (-), U802.3 (VREFPS)
unnamed: C809.1, C811.1, FB803.2, R803.2, U801.8 (V+)
unnamed: C810.1, C812.1, FB804.2, R804.2, U801.4 (V-)
unnamed: C817.1, U802.1 (INV), U803.2 (-)
unnamed: R808.1, U802.20 (RFB)
unnamed: U802.2 (VOUT), U803.3 (+)
unnamed: U801.1, U802.16 (VREFNF)
unnamed: U801.7, U802.4 (VREFPF)
unnamed: U1001.1, U1002.5
unnamed: U1002.3, U1002.4, U1003.3 (+)
unnamed: C1013.1, U1002.1, U1002.2, U1003.2 (-)
unnamed: U1002.6, U1003.6 (-), U1003.7
unnamed: C1013.2, U1003.1, U1004.3 (+)
unnamed: R1001.1, U1004.2 (-)
unnamed: U1101.9 (QH'), U1102.14 (SER)
unnamed: U1101.12 (RCLK), U1102.12 (RCLK), U1103.12 (RCLK), U1104.12 (RCLK), U1107.3 (A)
unnamed: U1101.14 (SER), U1103.9 (QH')
unnamed: U1101.11 (SRCLK), U1102.11 (SRCLK), U1103.11 (SRCLK), U1104.11 (SRCLK), U1106.3 (A)
unnamed: R1101.1, R1102.1, R1103.1, R1104.1, R1105.1, R1107.1, U1101.13 (~OE), U1102.13 (~OE), U1103.13 (~OE), U1104.13 (~OE)
unnamed: U1102.9 (QH'), U1108.3 (A)
unnamed: U1103.14 (SER), U1104.9 (QH')
unnamed: U1104.14 (SER), U1105.3 (A)
unnamed: R1106.1, U1108.5 (DIR)
unnamed: R1107.2, U1109.3 (A)
VCCQ: C307.1, C308.1, C309.1, C310.1, C311.1, C312.1, FB301.2, L301.2 (CTD), L301.7 (CRD), R315.1, R316.1, R317.1, R318.1, U301.1 (VDD2A), U301.19 (VDD1A)

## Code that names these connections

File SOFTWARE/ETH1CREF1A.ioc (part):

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Mcu.Name=STM32F429ZITx
Mcu.Package=LQFP144
Mcu.UserName=STM32F429ZITx
PA1.Mode=RMII
PA1.Signal=ETH_REF_CLK
PA13.Mode=Serial_Wire
PA13.Signal=SYS_JTMS-SWDIO
PA14.Mode=Serial_Wire
PA14.Signal=SYS_JTCK-SWCLK
PA2.Mode=RMII
PA2.Signal=ETH_MDIO
PA4.Mode=NSS_Signal_Hard_Output
PA4.Signal=SPI3_NSS
PA7.Mode=RMII
PA7.Signal=ETH_CRS_DV
PA8.Mode=I2C
PA8.Signal=I2C3_SCL
PB12.Mode=NSS_Signal_Hard_Output
PB12.Signal=SPI2_NSS
PB13.Mode=Full_Duplex_Master
PB13.Signal=SPI2_SCK
PB14.Mode=Full_Duplex_Master
PB14.Signal=SPI2_MISO
PB15.Mode=Full_Duplex_Master
PB15.Signal=SPI2_MOSI
PB6.Mode=I2C
PB6.Signal=I2C1_SCL
PB7.Mode=I2C
PB7.Signal=I2C1_SDA
PC1.Mode=RMII
PC1.Signal=ETH_MDC
PC10.Mode=Full_Duplex_Master
PC10.Signal=SPI3_SCK
PC11.Mode=Full_Duplex_Master
PC11.Signal=SPI3_MISO
PC12.Mode=Full_Duplex_Master
PC12.Signal=SPI3_MOSI
PC4.Mode=RMII
PC4.Signal=ETH_RXD0
PC5.Mode=RMII
PC5.Signal=ETH_RXD1
PC9.Mode=I2C
PC9.Signal=I2C3_SDA
PF0.Mode=I2C
PF0.Signal=I2C2_SDA
PF1.Mode=I2C
PF1.Signal=I2C2_SCL
PF7.Mode=Full_Duplex_Master
PF7.Signal=SPI5_SCK
PF8.Mode=Full_Duplex_Master
PF8.Signal=SPI5_MISO
PF9.Mode=Full_Duplex_Master
PF9.Signal=SPI5_MOSI
PG11.Mode=RMII
PG11.Signal=ETH_TX_EN
PG13.Mode=RMII
PG13.Signal=ETH_TXD0
PG14.Mode=RMII
PG14.Signal=ETH_TXD1
PH0/OSC_IN.Mode=HSE-External-Oscillator
PH0/OSC_IN.Signal=RCC_OSC_IN
PH1/OSC_OUT.Mode=HSE-External-Oscillator
PH1/OSC_OUT.Signal=RCC_OSC_OUT
RCC.HSE_VALUE=16000000
RCC.SYSCLKFreq_VALUE=180000000
RCC.SYSCLKSource=RCC_SYSCLKSOURCE_PLLCLK
board=custom

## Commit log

2023-06-30 Hardware
2023-07-02 Hardware and software
